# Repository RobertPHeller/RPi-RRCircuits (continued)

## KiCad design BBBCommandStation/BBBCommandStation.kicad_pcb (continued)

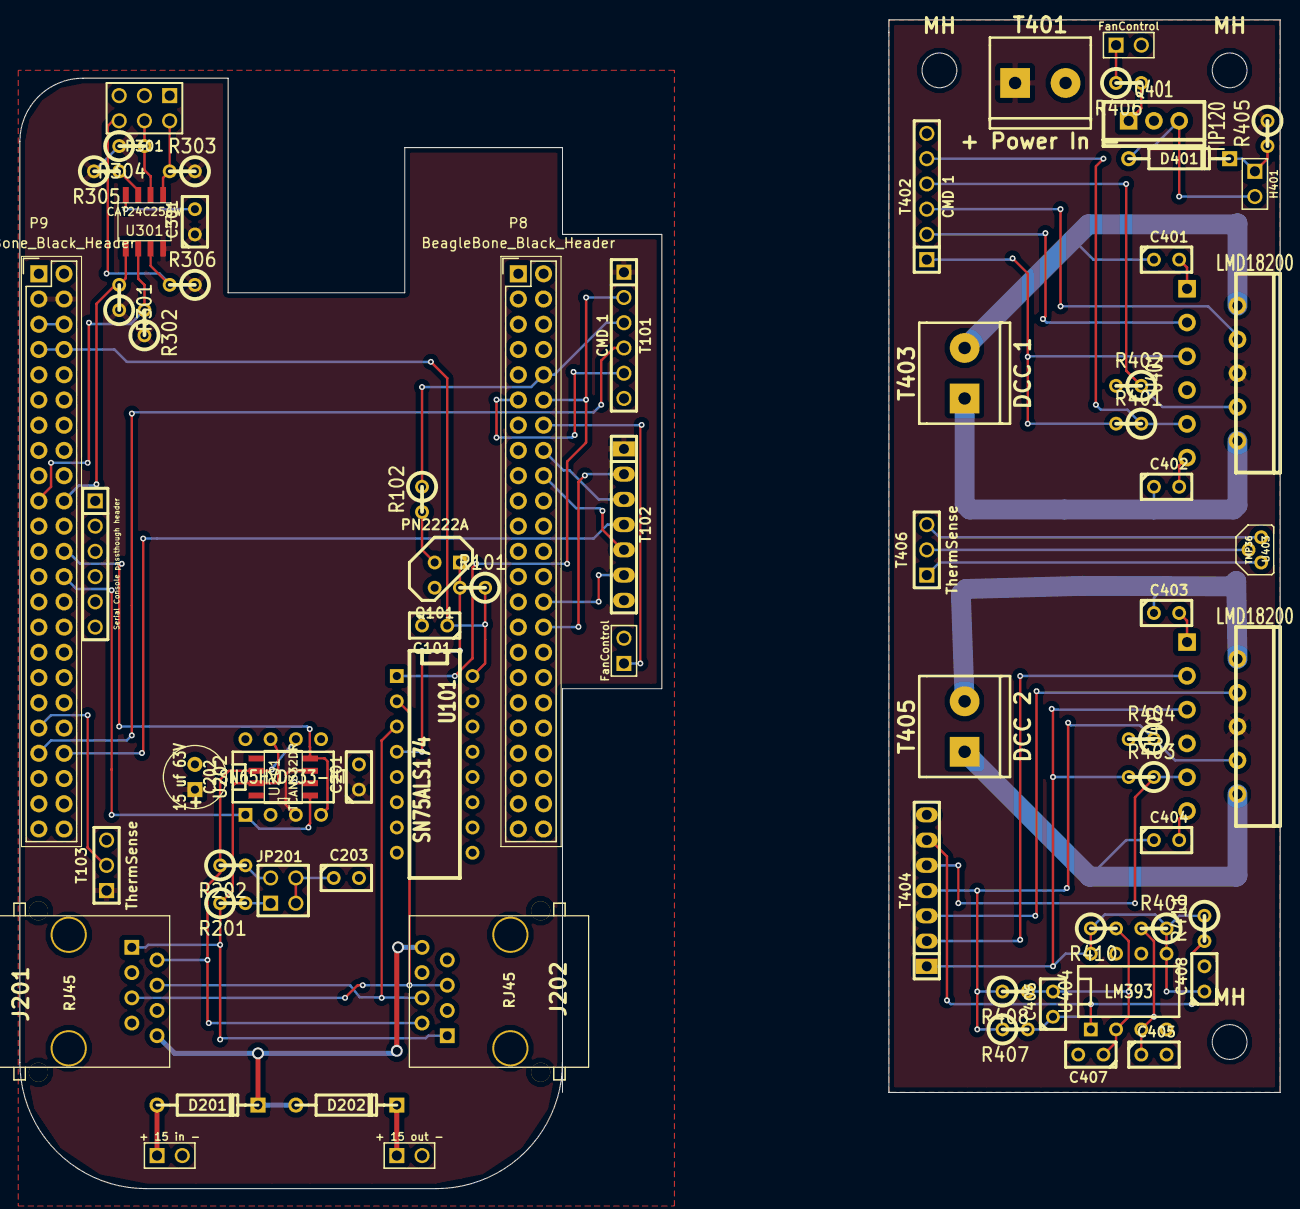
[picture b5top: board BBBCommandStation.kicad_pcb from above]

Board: 2 copper layers, 126.8 x 117.6 mm, 71 parts (0 on the bottom side), 65 nets.

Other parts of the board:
MH: MountingHole_3-5mm_RevA_Date21Jun2010
MH#2, MH#3: MountingHole_3-5mm_RevA_Date21Jun2010
PIN_ARRAY-6X1: Serial Console passthough header; PIN_ARRAY-6X1

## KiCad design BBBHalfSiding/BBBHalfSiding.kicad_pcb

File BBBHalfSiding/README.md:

# BBBHalfSiding

Early HalfSiding cape for the Beagle Bone Black. A somewhat all-in-one board
for the Beagle Bone Black to manage one half of a siding. This something of a
"kitchen sink" board and proably awkard in practice. Probably better off
stacking several separate special purpose capes.  I mostly did this as a 
"thought experiment" to see what this would look like.  Oh, if it used SMD 
parts it might be more compact and might be practical as a single board.

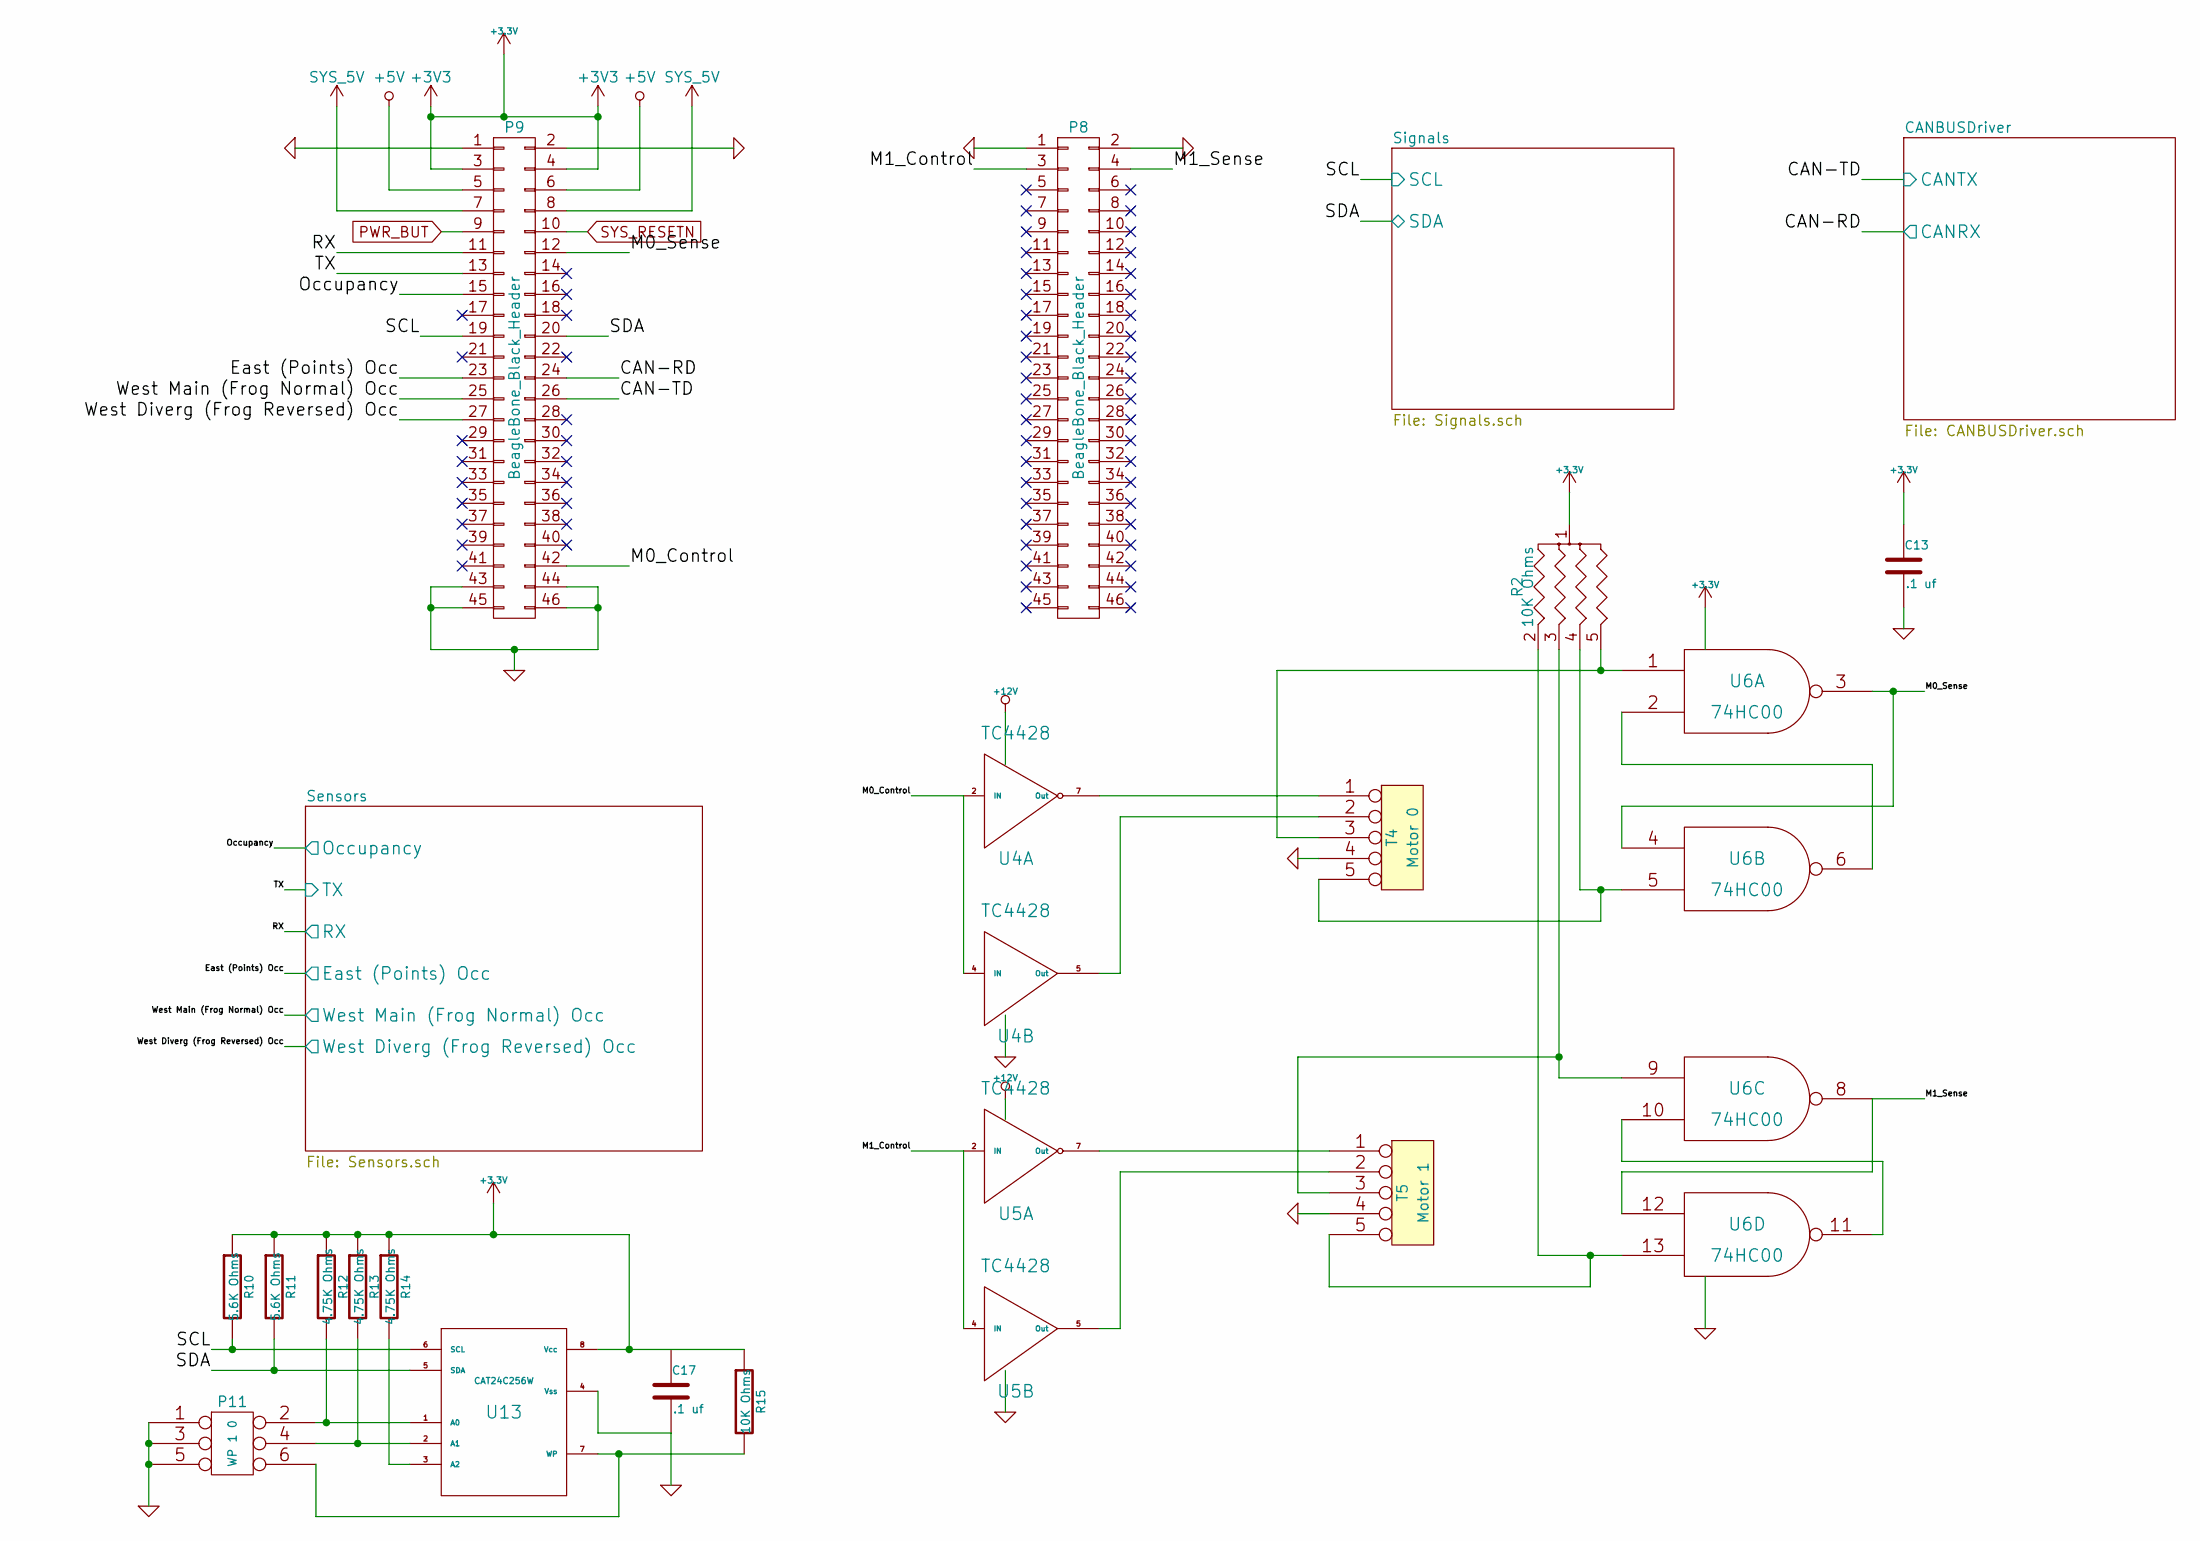
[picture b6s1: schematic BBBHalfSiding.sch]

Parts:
C13, C17: .1 uf
P8, P9: BeagleBone_Black_Header; Socket_BeagleBone_Black
P11: WP 1 0
R2: 10K Ohms
R10, R11: 5.6K Ohms
R12, R13, R14: 4.75K Ohms
R15: 10K Ohms
T4: Motor 0
T5: Motor 1
U4, U5: TC4428
U6: 74HC00
U13: CAT24C256W

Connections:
+3.3V: C13.1, P9.3, P9.4, R2.1, R10.1, R11.1, R12.1, R13.1, R14.1, R15.1, U6.14 (VCC), U13.8 (Vcc); also elsewhere on the board
+5V: P9.5, P9.6; also elsewhere on the board
+12V: U4.6 (Vdd), U5.6 (Vdd); also elsewhere on the board
/CANBUSDriver/CANRX: P9.24; also elsewhere on the board
/CANBUSDriver/CANTX: P9.26; also elsewhere on the board
/M0_Control: P9.42, U4.2 (IN), U4.4 (IN)
/M0_Sense: P9.12, U6.3, U6.4
/M1_Control: P8.3, U5.2 (IN), U5.4 (IN)
/M1_Sense: P8.4, U6.8, U6.12
/Sensors/East (Points) Occ: P9.23; also elsewhere on the board
/Sensors/Occupancy: P9.15; also elsewhere on the board
/Sensors/RX: P9.11; also elsewhere on the board
/Sensors/TX: P9.13; also elsewhere on the board
/Sensors/West Diverg (Frog Reversed) Occ: P9.27; also elsewhere on the board
/Sensors/West Main (Frog Normal) Occ: P9.25; also elsewhere on the board
/Signals/SCL: P9.19, R10.2, U13.6 (SCL); also elsewhere on the board
/Signals/SDA: P9.20, R11.2, U13.5 (SDA); also elsewhere on the board
GND: C13.2, C17.2, P8.1, P8.2, P9.1, P9.2, P9.43, P9.44, P9.45, P9.46, P11.1, P11.3, P11.5, T4.4, T5.4, U4.3 (GND), U5.3 (GND), U6.7 (GND), U13.4 (Vss); also elsewhere on the board
unnamed: T5.2, U5.5 (Out)
unnamed: T5.1, U5.7 (Out)
unnamed: T4.2, U4.5 (Out)
unnamed: T4.1, U4.7 (Out)
unnamed: P11.2, R12.2, U13.1 (A0)
unnamed: R2.4, T4.5, U6.5
unnamed: R2.5, T4.3, U6.1
unnamed: U6.2, U6.6
unnamed: U6.10, U6.11
unnamed: R14.2, U13.3 (A2)
unnamed: P11.4, R13.2, U13.2 (A1)
unnamed: P11.6, R15.2, U13.7 (WP)
unnamed: R2.2, T5.5, U6.13
unnamed: R2.3, T5.3, U6.9
SYS_5V: P9.7, P9.8

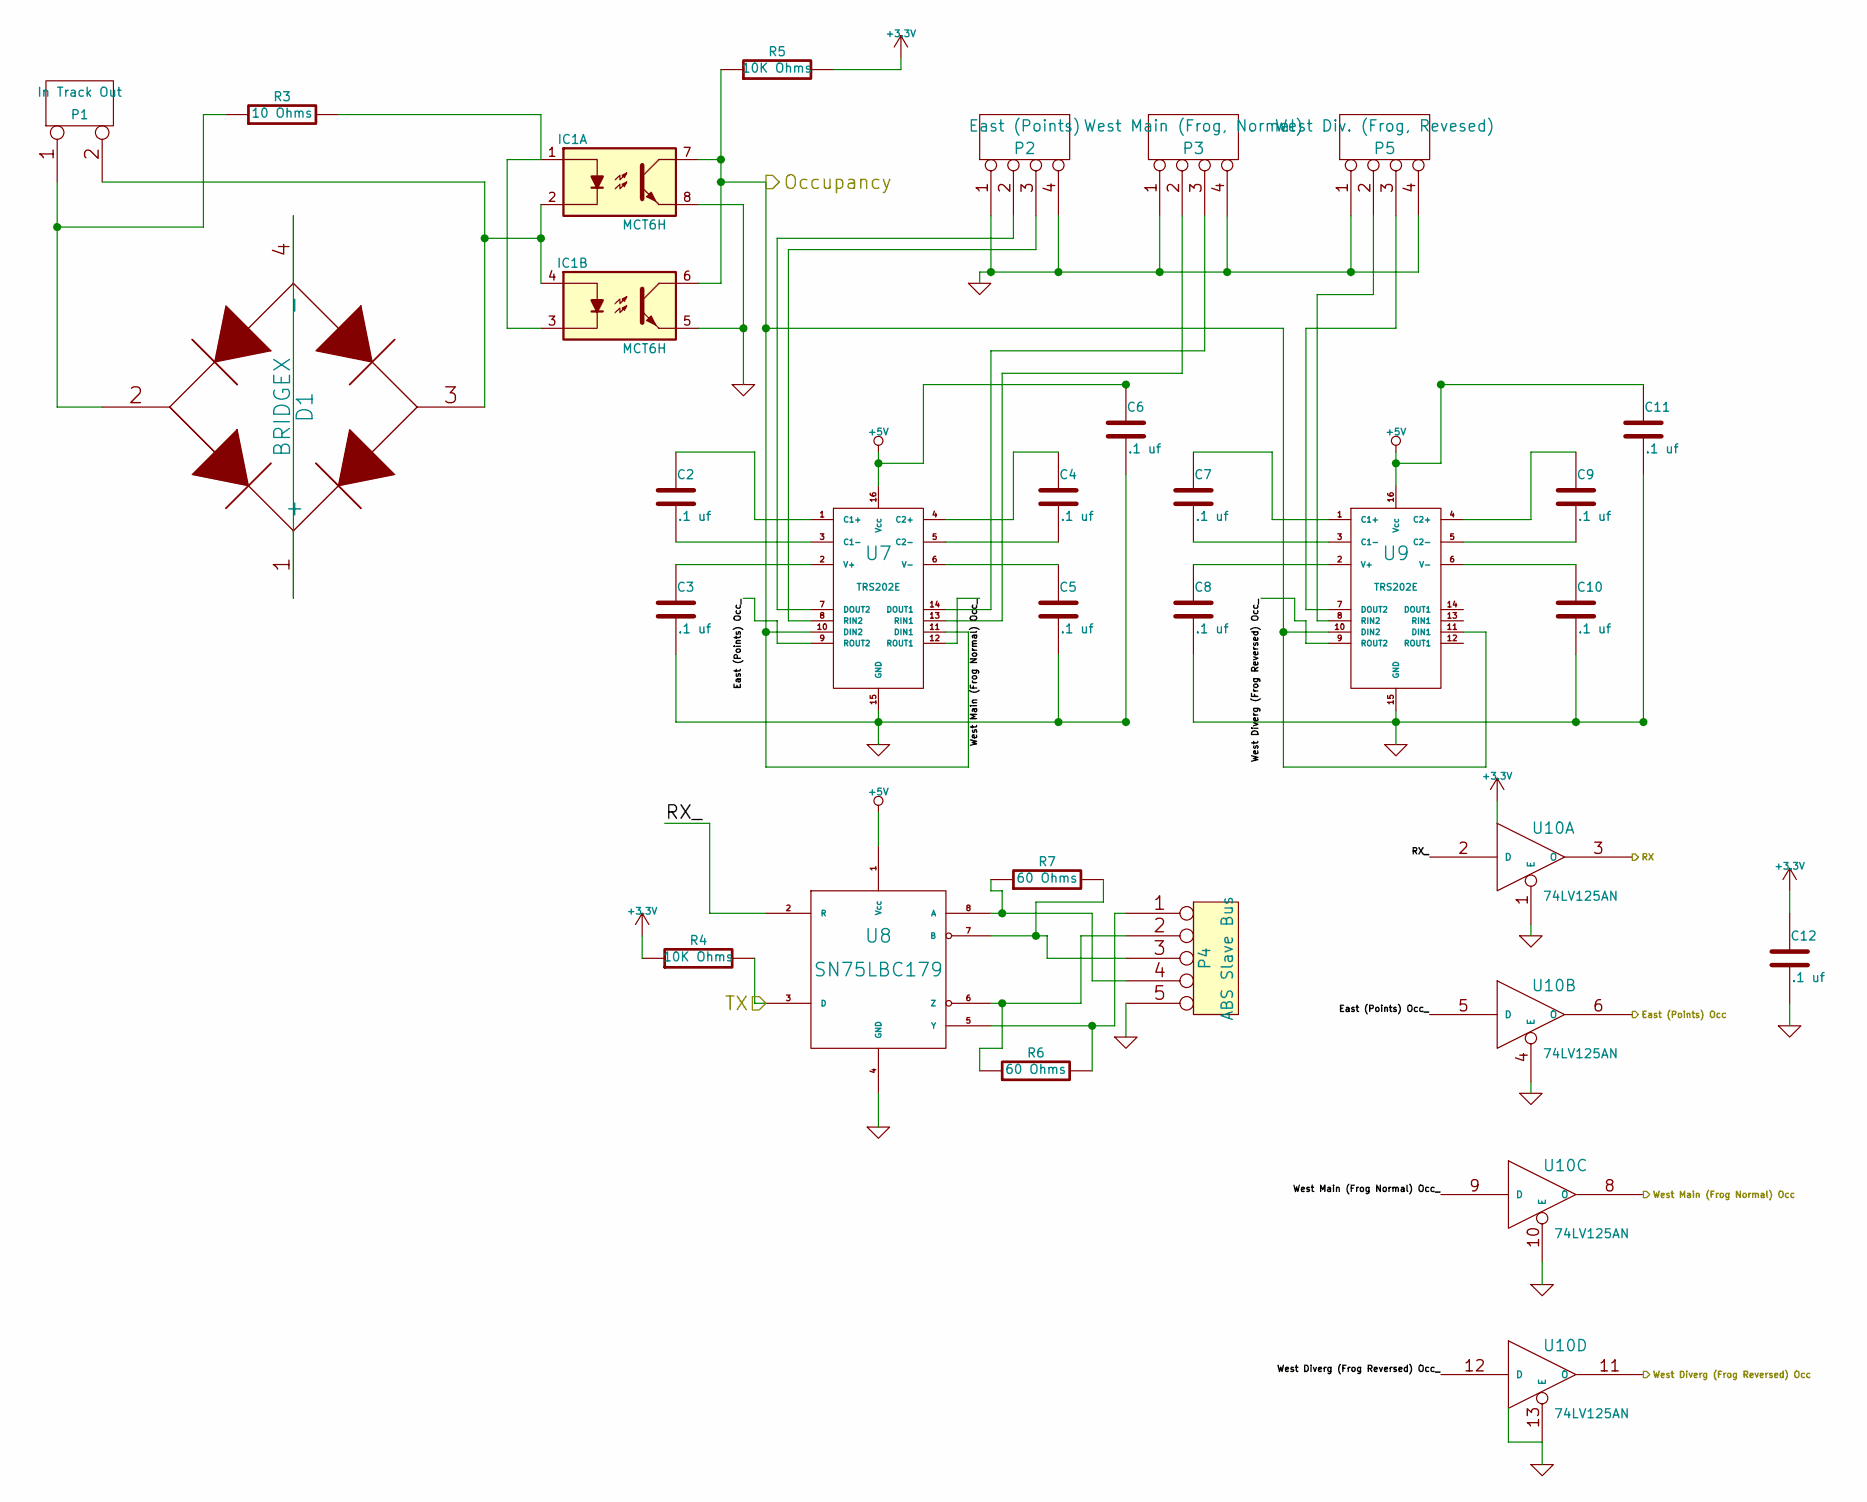
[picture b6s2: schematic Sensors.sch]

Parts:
C2, C3, C4, C5, C6, C7, C8, C9, C10, C11, C12: .1 uf
D1: BRIDGEX
IC1: MCT6H; DIP-8__300
P1: In Track Out
P2: East (Points)
P3: West Main (Frog, Normal)
P4: ABS Slave Bus
P5: West Div. (Frog, Revesed)
R3: 10 Ohms
R4, R5: 10K Ohms
R6, R7: 60 Ohms
U7, U9: TRS202E
U8: SN75LBC179
U10: 74LV125AN

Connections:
+3.3V: C12.1, R4.1, R5.2, U10.14 (VCC); also elsewhere on the board
+5V: C6.1, C11.1, U7.16 (Vcc), U8.1 (Vcc), U9.16 (Vcc); also elsewhere on the board
/Sensors/East (Points) Occ: U10.6 (O); also elsewhere on the board
/Sensors/East (Points) Occ_: U7.9 (ROUT2), U10.5 (D)
/Sensors/Occupancy: IC1.6, IC1.7, R5.1, U7.10 (DIN2), U7.11 (DIN1), U9.10 (DIN2), U9.11 (DIN1); also elsewhere on the board
/Sensors/RX: U10.3 (O); also elsewhere on the board
/Sensors/RX_: U8.2 (R), U10.2 (D)
/Sensors/TX: R4.2, U8.3 (D); also elsewhere on the board
/Sensors/West Diverg (Frog Reversed) Occ: U10.11 (O); also elsewhere on the board
/Sensors/West Diverg (Frog Reversed) Occ_: U9.9 (ROUT2), U10.12 (D)
/Sensors/West Main (Frog Normal) Occ: U10.8 (O); also elsewhere on the board
/Sensors/West Main (Frog Normal) Occ_: U7.12 (ROUT1), U10.9 (D)
GND: C3.2, C5.2, C6.2, C8.2, C10.2, C11.2, C12.2, IC1.5, IC1.8, P2.1, P2.4, P3.1, P3.4, P4.5, P5.1, P5.4, U7.15 (GND), U8.4 (GND), U9.15 (GND), U10.1 (E), U10.4 (E), U10.7 (GND), U10.10 (E), U10.13 (E); also elsewhere on the board
unnamed: P3.3, U7.14 (DOUT1)
unnamed: P5.3, U9.7 (DOUT2)
unnamed: P2.3, U7.8 (RIN2)
unnamed: P2.2, U7.7 (DOUT2)
unnamed: P5.2, U9.8 (RIN2)
unnamed: P3.2, U7.13 (RIN1)
unnamed: C9.1, U9.4 (C2+)
unnamed: C7.1, U9.1 (C1+)
unnamed: C10.1, U9.6 (V-)
unnamed: C9.2, U9.5 (C2-)
unnamed: C8.1, U9.2 (V+)
unnamed: C7.2, U9.3 (C1-)
unnamed: D1.1 (+), D1.4 (-)
unnamed: IC1.1, IC1.3, R3.2
unnamed: P4.1, R6.2, U8.5 (Y)
unnamed: C4.1, U7.4 (C2+)
unnamed: C2.1, U7.1 (C1+)
unnamed: C5.1, U7.6 (V-)
unnamed: C4.2, U7.5 (C2-)
unnamed: C3.1, U7.2 (V+)
unnamed: C2.2, U7.3 (C1-)
unnamed: P4.2, R6.1, U8.6 (Z)
unnamed: D1.2, P1.1, R3.1
unnamed: D1.3, IC1.2, IC1.4, P1.2 (PM)
unnamed: P4.3, R7.2, U8.7 (B)
unnamed: P4.4, R7.1, U8.8 (A)

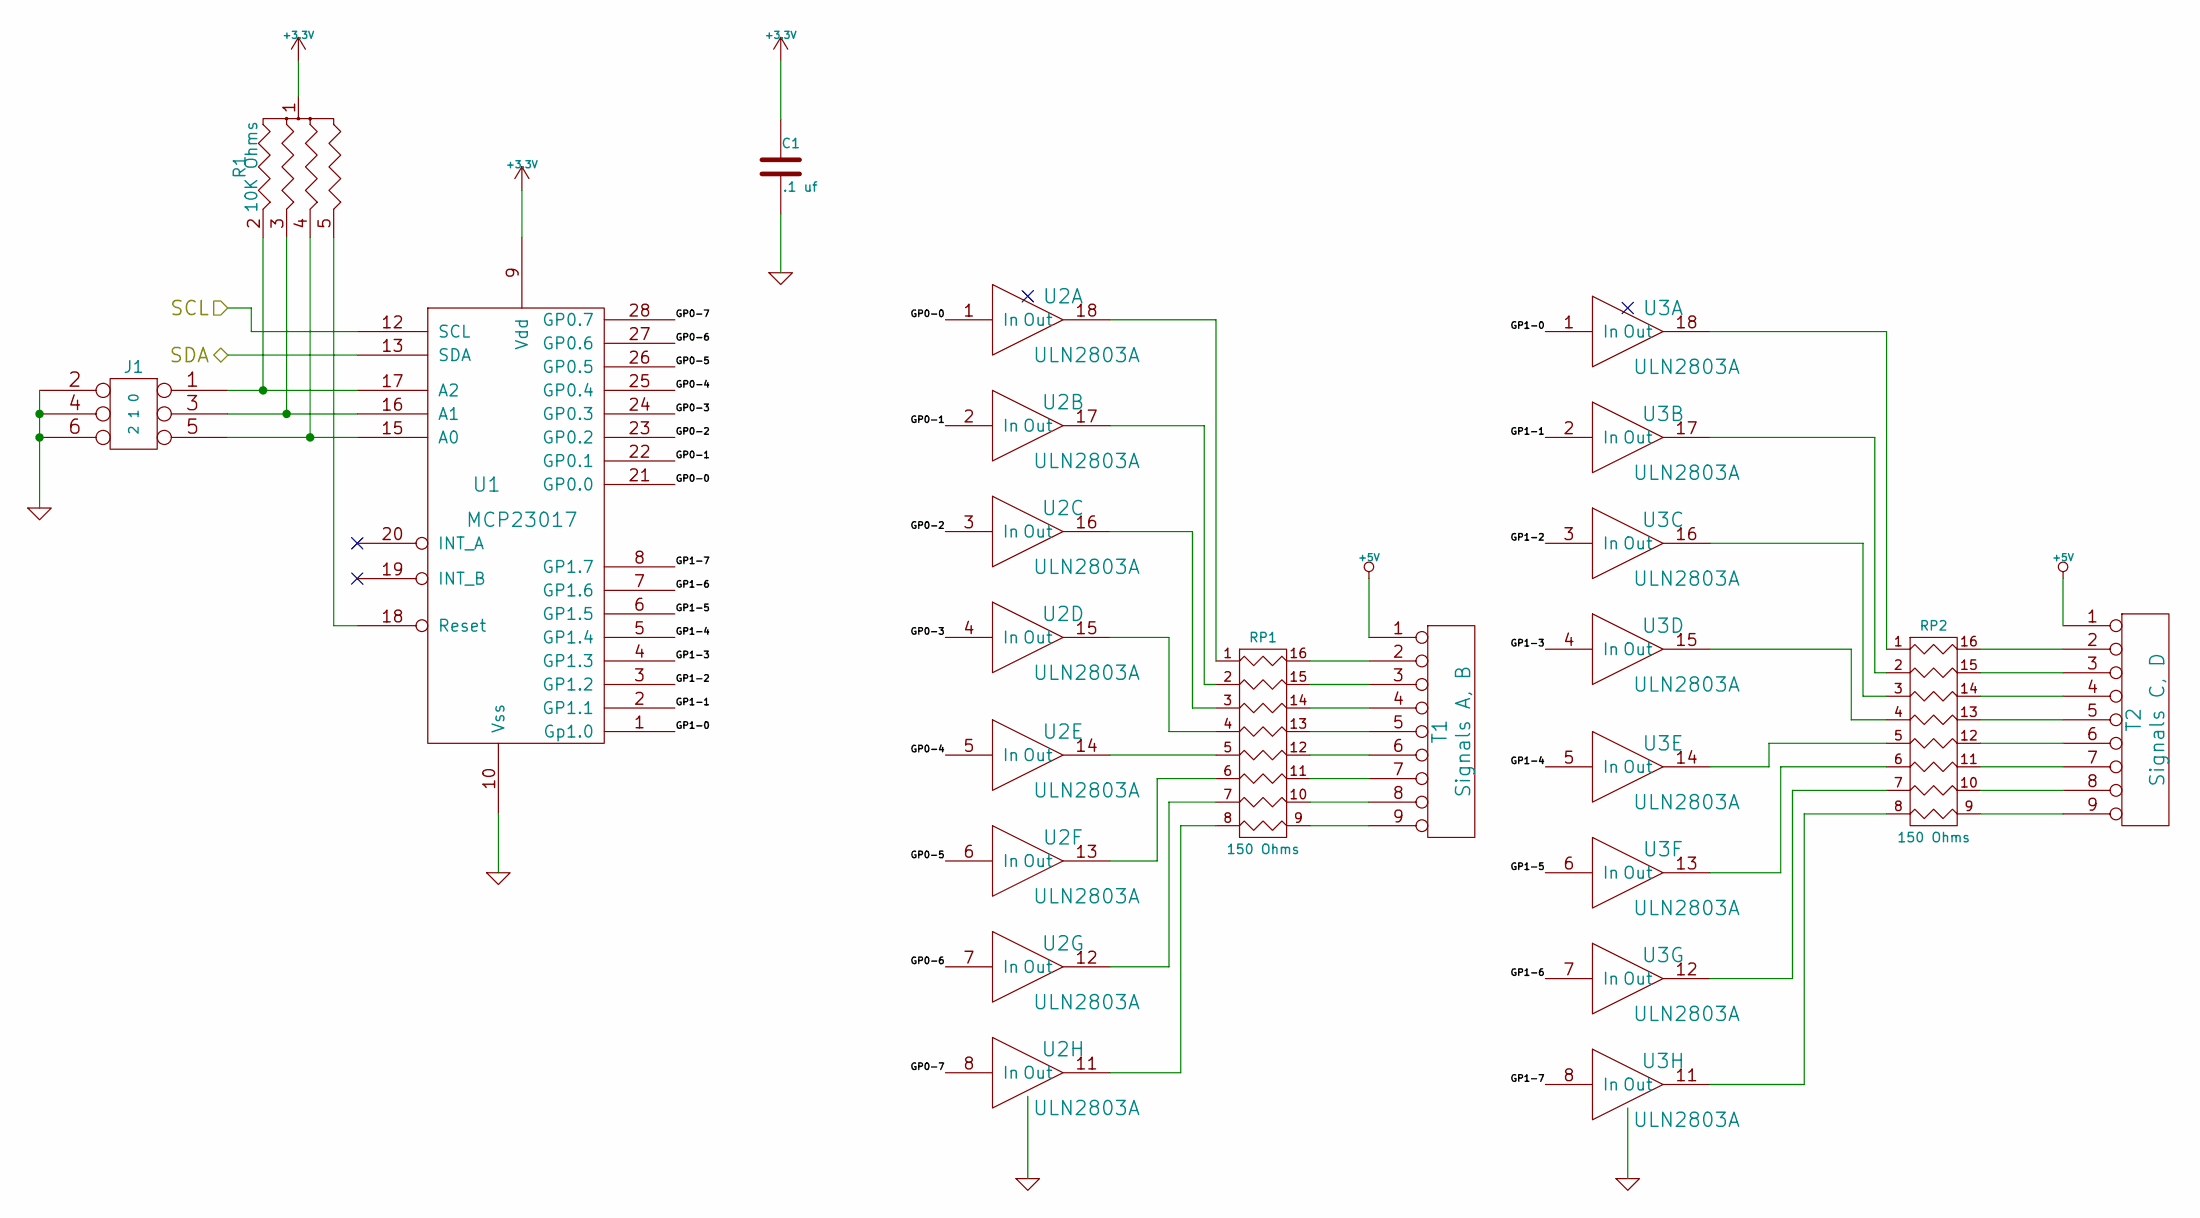
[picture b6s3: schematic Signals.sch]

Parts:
C1: .1 uf
J1: 2 1 0
R1: 10K Ohms
RP1, RP2: 150 Ohms
T1: Signals A, B
T2: Signals C, D
U1: MCP23017
U2, U3: ULN2803A

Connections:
+3.3V: C1.1, R1.1, U1.9 (Vdd); also elsewhere on the board
+5V: T1.1, T2.1; also elsewhere on the board
/Signals/GP0-0: U1.21 (GP0.0), U2.1 (In)
/Signals/GP0-1: U1.22 (GP0.1), U2.2 (In)
/Signals/GP0-2: U1.23 (GP0.2), U2.3 (In)
/Signals/GP0-3: U1.24 (GP0.3), U2.4 (In)
/Signals/GP0-4: U1.25 (GP0.4), U2.5 (In)
/Signals/GP0-5: U1.26 (GP0.5), U2.6 (In)
/Signals/GP0-6: U1.27 (GP0.6), U2.7 (In)
/Signals/GP0-7: U1.28 (GP0.7), U2.8 (In)
/Signals/GP1-0: U1.1 (Gp1.0), U3.1 (In)
/Signals/GP1-1: U1.2 (GP1.1), U3.2 (In)
/Signals/GP1-2: U1.3 (GP1.2), U3.3 (In)
/Signals/GP1-3: U1.4 (GP1.3), U3.4 (In)
/Signals/GP1-4: U1.5 (GP1.4), U3.5 (In)
/Signals/GP1-5: U1.6 (GP1.5), U3.6 (In)
/Signals/GP1-6: U1.7 (GP1.6), U3.7 (In)
/Signals/GP1-7: U1.8 (GP1.7), U3.8 (In)
/Signals/SCL: U1.12 (SCL); also elsewhere on the board
/Signals/SDA: U1.13 (SDA); also elsewhere on the board
GND: C1.2, J1.2, J1.4, J1.6, U1.10 (Vss), U2.9 (GND), U3.9 (GND); also elsewhere on the board
unnamed: R1.5, U1.18 (Reset)
unnamed: J1.1, R1.2, U1.17 (A2)
unnamed: RP1.12 (R5), T1.6
unnamed: RP1.13 (R4), T1.5
unnamed: RP1.14 (R3), T1.4
unnamed: RP1.15 (R2), T1.3
unnamed: RP1.16 (R1), T1.2
unnamed: RP2.9 (R8), T2.9
unnamed: RP2.10 (R7), T2.8
unnamed: RP2.11 (R6), T2.7
unnamed: RP2.12 (R5), T2.6
unnamed: RP2.13 (R4), T2.5
unnamed: RP2.14 (R3), T2.4
unnamed: RP2.15 (R2), T2.3
unnamed: RP2.16 (R1), T2.2
unnamed: RP1.9 (R8), T1.9
unnamed: RP1.10 (R7), T1.8
unnamed: RP1.11 (R6), T1.7
unnamed: J1.5, R1.4, U1.15 (A0)
unnamed: J1.3, R1.3, U1.16 (A1)
unnamed: RP2.8, U3.11 (Out)
unnamed: RP2.7, U3.12 (Out)
unnamed: RP2.6, U3.13 (Out)
unnamed: RP1.7, U2.12 (Out)
unnamed: RP1.6, U2.13 (Out)
unnamed: RP1.5, U2.14 (Out)
unnamed: RP1.4, U2.15 (Out)
unnamed: RP1.3, U2.16 (Out)
unnamed: RP1.2, U2.17 (Out)
unnamed: RP1.1, U2.18 (Out)
unnamed: RP2.5, U3.14 (Out)
unnamed: RP2.4, U3.15 (Out)
unnamed: RP2.3, U3.16 (Out)
unnamed: RP2.2, U3.17 (Out)
unnamed: RP2.1, U3.18 (Out)
unnamed: RP1.8, U2.11 (Out)

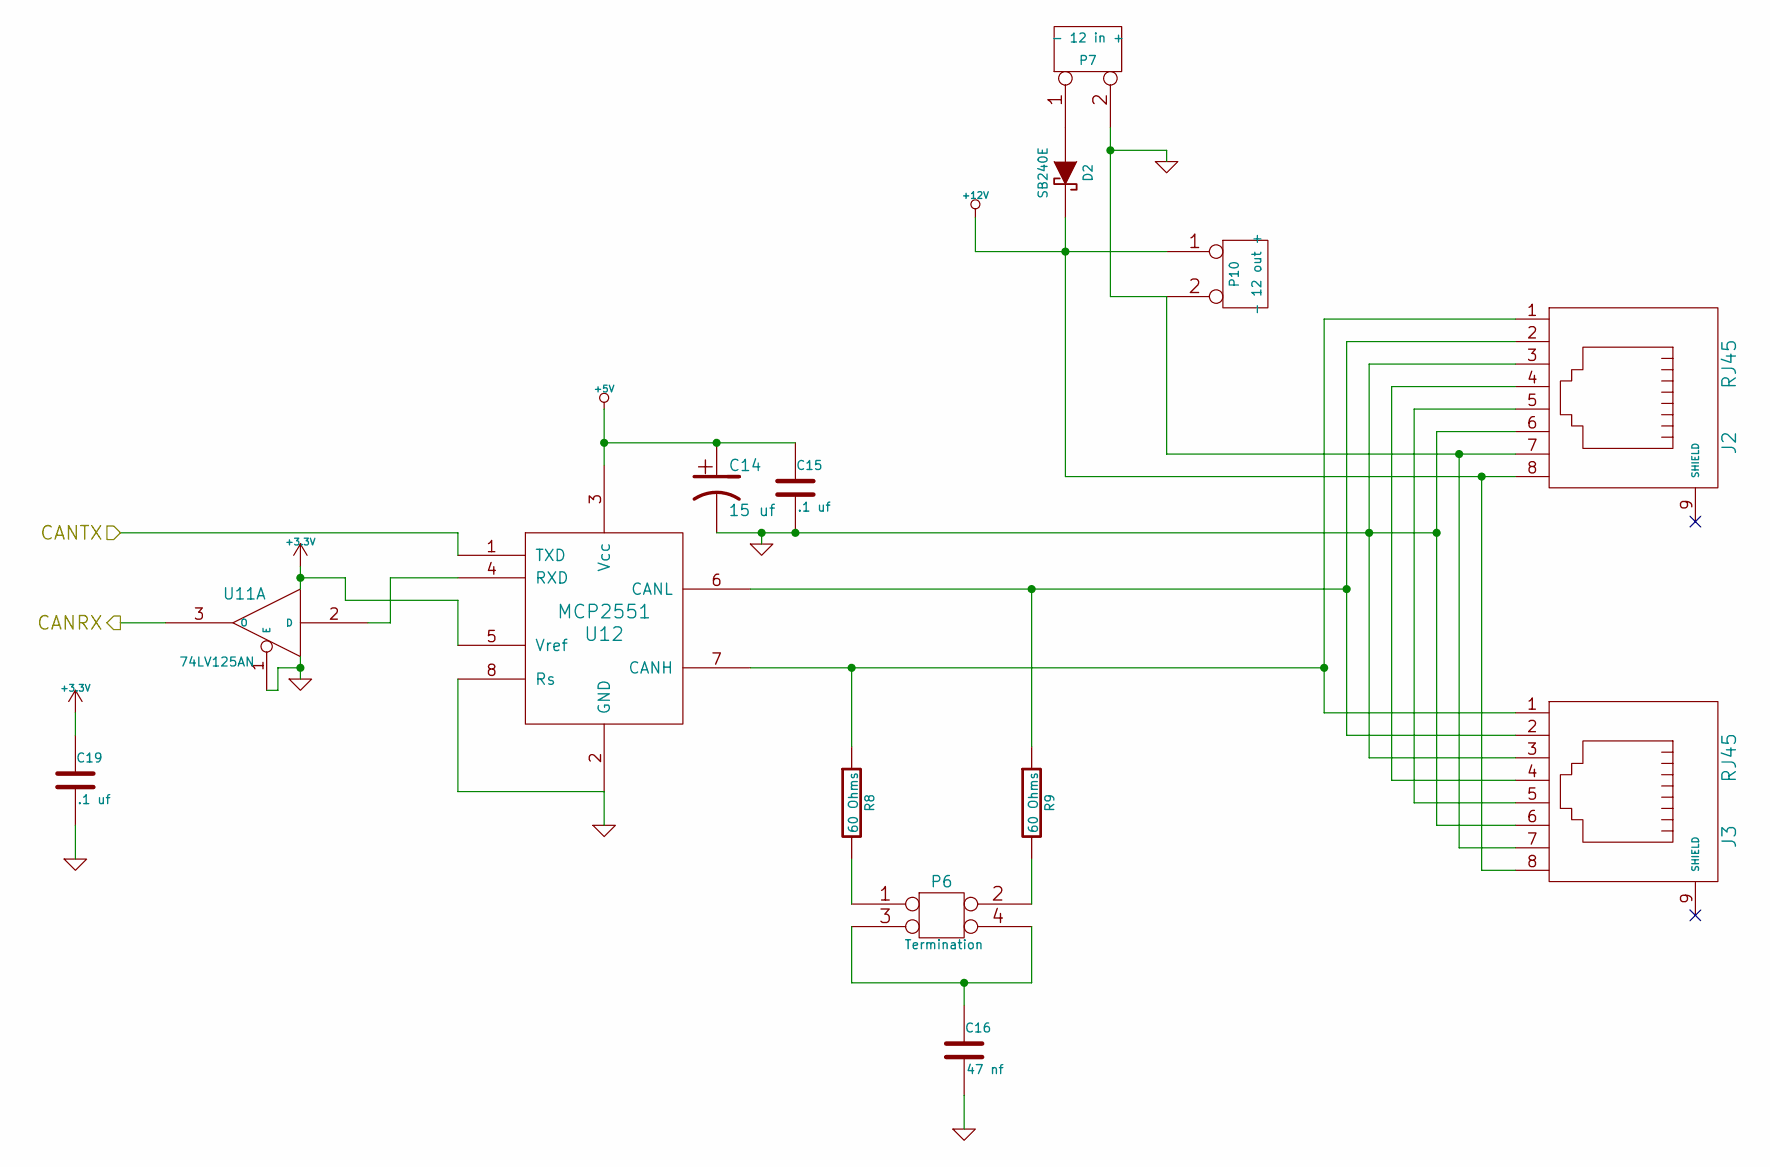
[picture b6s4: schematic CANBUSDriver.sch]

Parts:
C14: 15 uf; Mouser Part Number 98-156CKR050M
C15, C19: .1 uf
C16: 47 nf
D2: SB240E; Mouser Part Number 625-SB240-E3/73
J2, J3: RJ45
P6: Termination
P7: - 12 in +
P10: - 12 out +
R8, R9: 60 Ohms
U11: 74LV125AN
U12: MCP2551; DIL-8_300

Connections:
+3.3V: C19.1, U11.14 (VCC), U12.5 (Vref); also elsewhere on the board
+5V: C14.1, C15.1, U12.3 (Vcc); also elsewhere on the board
+12V: D2.2 (K), J2.8, J3.8, P10.1; also elsewhere on the board
/CANBUSDriver/CANRX: U11.3 (O); also elsewhere on the board
/CANBUSDriver/CANTX: U12.1 (TXD); also elsewhere on the board
GND: C14.2, C15.2, C16.2, C19.2, J2.3, J2.6, J2.7, J3.3, J3.6, J3.7, P7.2 (PM), P10.2 (PM), U11.1 (E), U11.7 (GND), U12.2 (GND), U12.8 (Rs); also elsewhere on the board
unnamed: J2.4, J3.4
unnamed: J2.5, J3.5
unnamed: J2.2, J3.2, R9.1, U12.6 (CANL)
unnamed: J2.1, J3.1, R8.1, U12.7 (CANH)
unnamed: D2.1 (A), P7.1
unnamed: U11.2 (D), U12.4 (RXD)
unnamed: C16.1, P6.3, P6.4
unnamed: P6.1, R8.2
unnamed: P6.2, R9.2

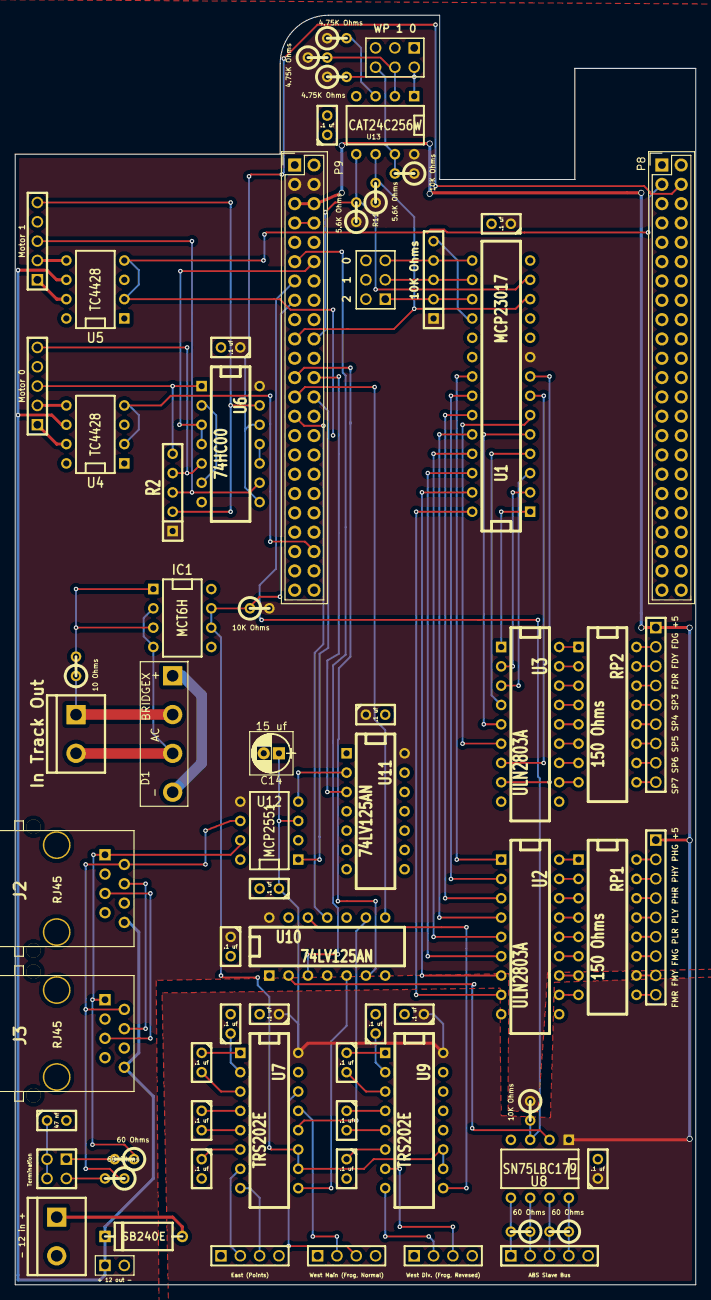
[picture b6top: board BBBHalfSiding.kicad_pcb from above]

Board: 2 copper layers, 89.4 x 166.9 mm, 70 parts (0 on the bottom side), 124 nets.

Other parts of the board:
C18: .1 uf; C1

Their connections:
+5V: C18.1; also elsewhere on the board
GND: C18.2; also elsewhere on the board
